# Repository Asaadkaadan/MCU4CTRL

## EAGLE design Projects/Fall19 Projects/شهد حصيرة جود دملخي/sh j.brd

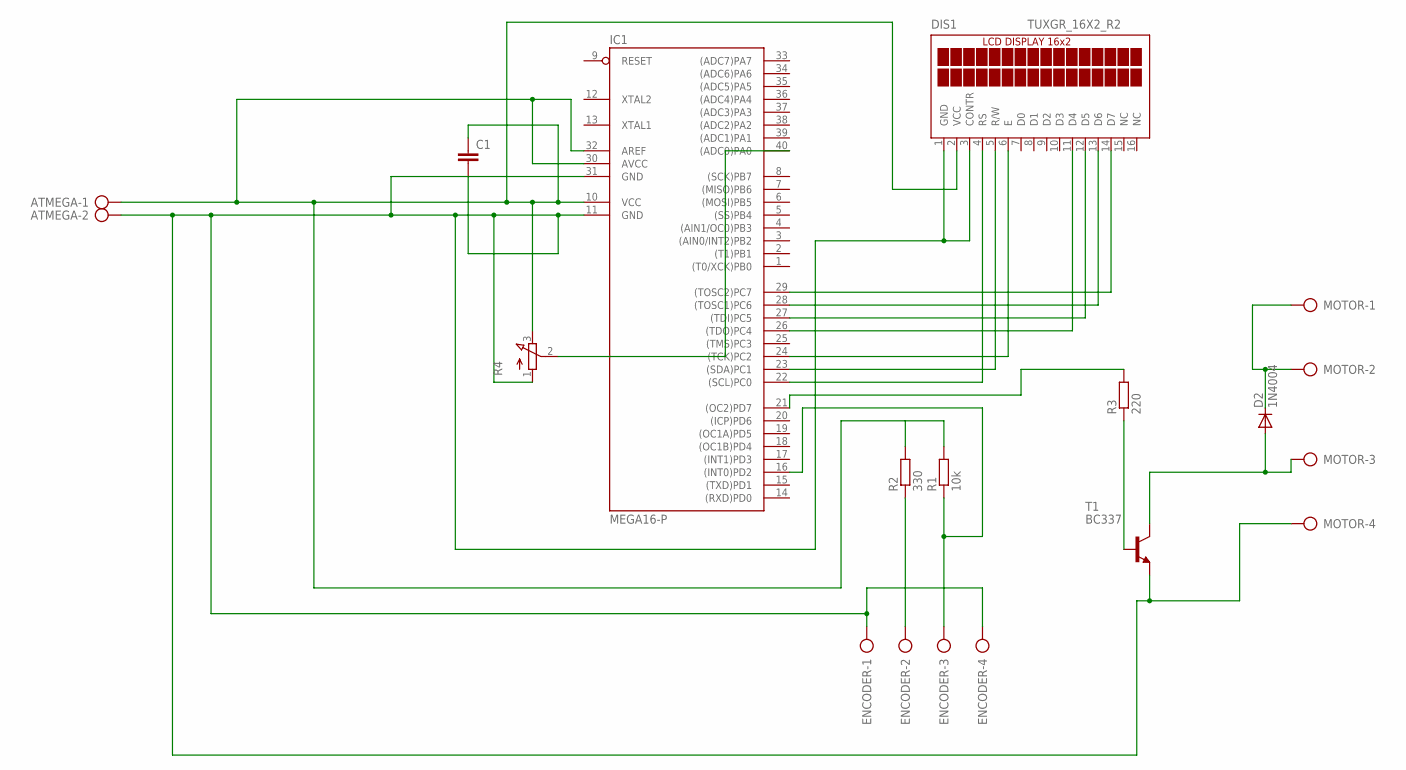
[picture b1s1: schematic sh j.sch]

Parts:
ATMEGA: AK500/2-H
C1: C-EU025-050X050; C025-050X050
D2: 1N4004; DO41-10
DIS1: TUXGR_16X2_R2
ENCODER: AK500/4-H
IC1: MEGA16-P; DIL40
MOTOR: AK500/4-H
R1: 10k; 0207/10
R2: 330; 0207/10
R3: 220; 0207/10
R4: 3RP/1610N
T1: BC337; TO92

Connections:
unnamed: DIS1.14 (D7), IC1.29 ((TOSC2)PC7)
unnamed: DIS1.13 (D6), IC1.28 ((TOSC1)PC6)
unnamed: DIS1.12 (D5), IC1.27 ((TDI)PC5)
unnamed: DIS1.11 (D4), IC1.26 ((TDO)PC4)
unnamed: DIS1.6 (E), IC1.24 ((TCK)PC2)
unnamed: DIS1.5 (R/W), IC1.23 ((SDA)PC1)
unnamed: DIS1.4 (RS), IC1.22 ((SCL)PC0)
unnamed: ATMEGA.2, C1.2, DIS1.1 (GND), DIS1.3 (CONTR), ENCODER.1, ENCODER.4, IC1.11 (GND), IC1.31 (GND), MOTOR.4, R4.1 (A), T1.1 (E)
unnamed: R3.1, T1.2 (B)
unnamed: IC1.21 ((OC2)PD7), R3.2
unnamed: ENCODER.3, IC1.16 ((INT0)PD2), R1.1
unnamed: D2.C, MOTOR.1, MOTOR.2
unnamed: D2.A, MOTOR.3, T1.3 (C)
unnamed: IC1.40 ((ADC0)PA0), R4.2 (S)
unnamed: ENCODER.2, R2.1
unnamed: ATMEGA.1, C1.1, DIS1.2 (VCC), IC1.10 (VCC), IC1.30 (AVCC), IC1.32 (AREF), R1.2, R2.2, R4.3 (E)

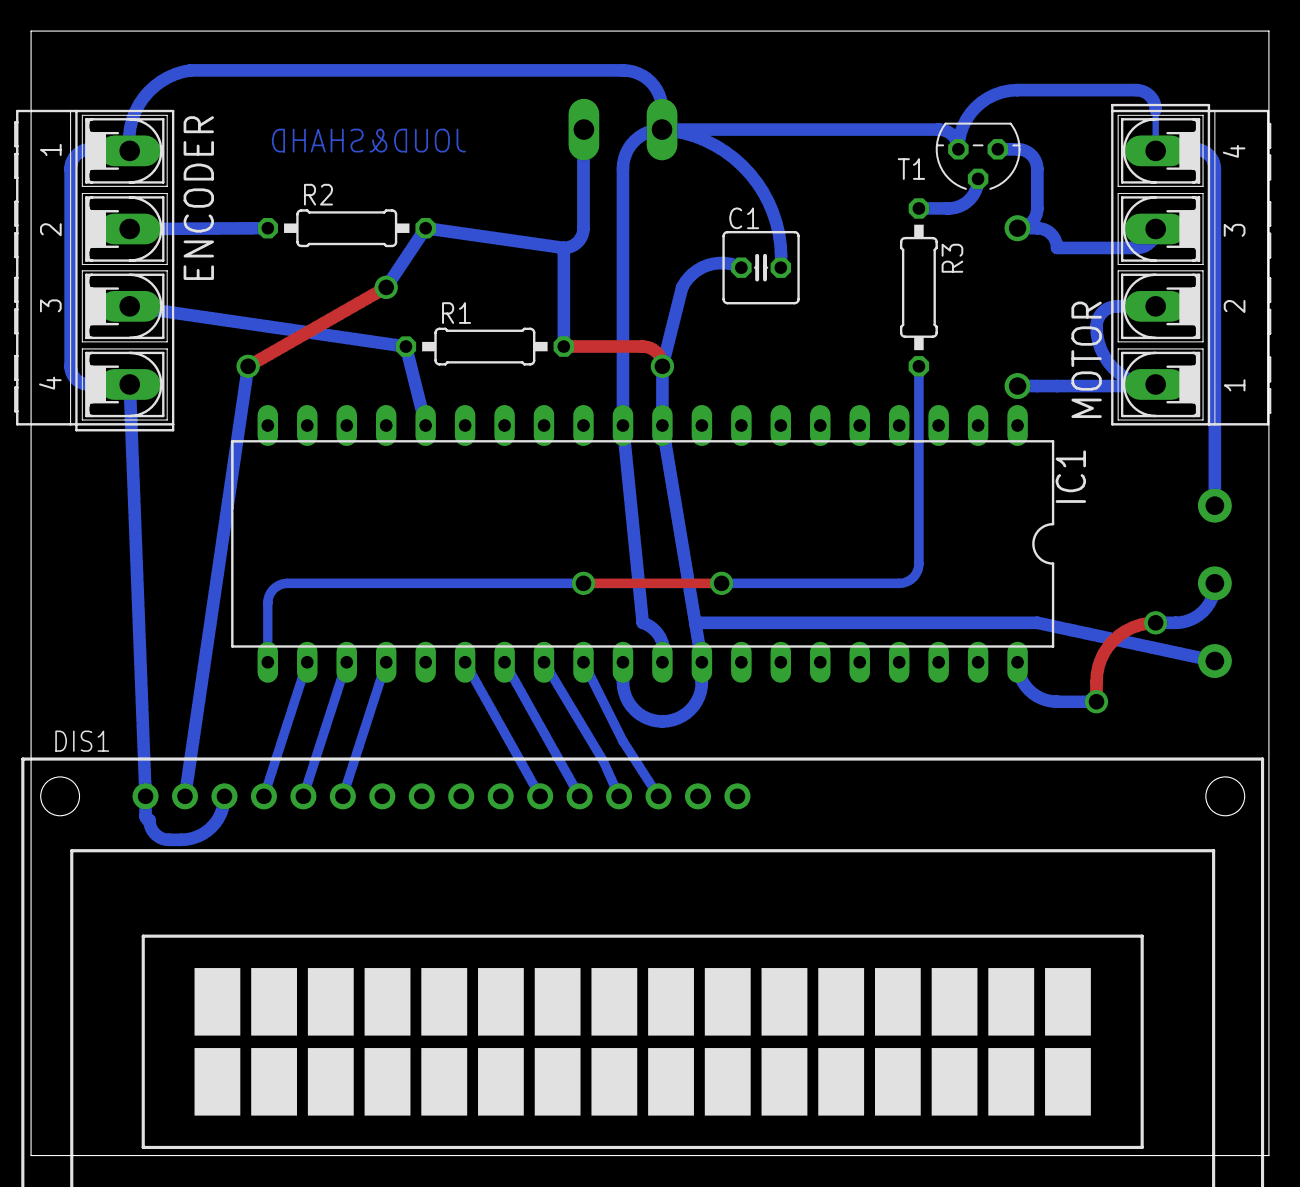
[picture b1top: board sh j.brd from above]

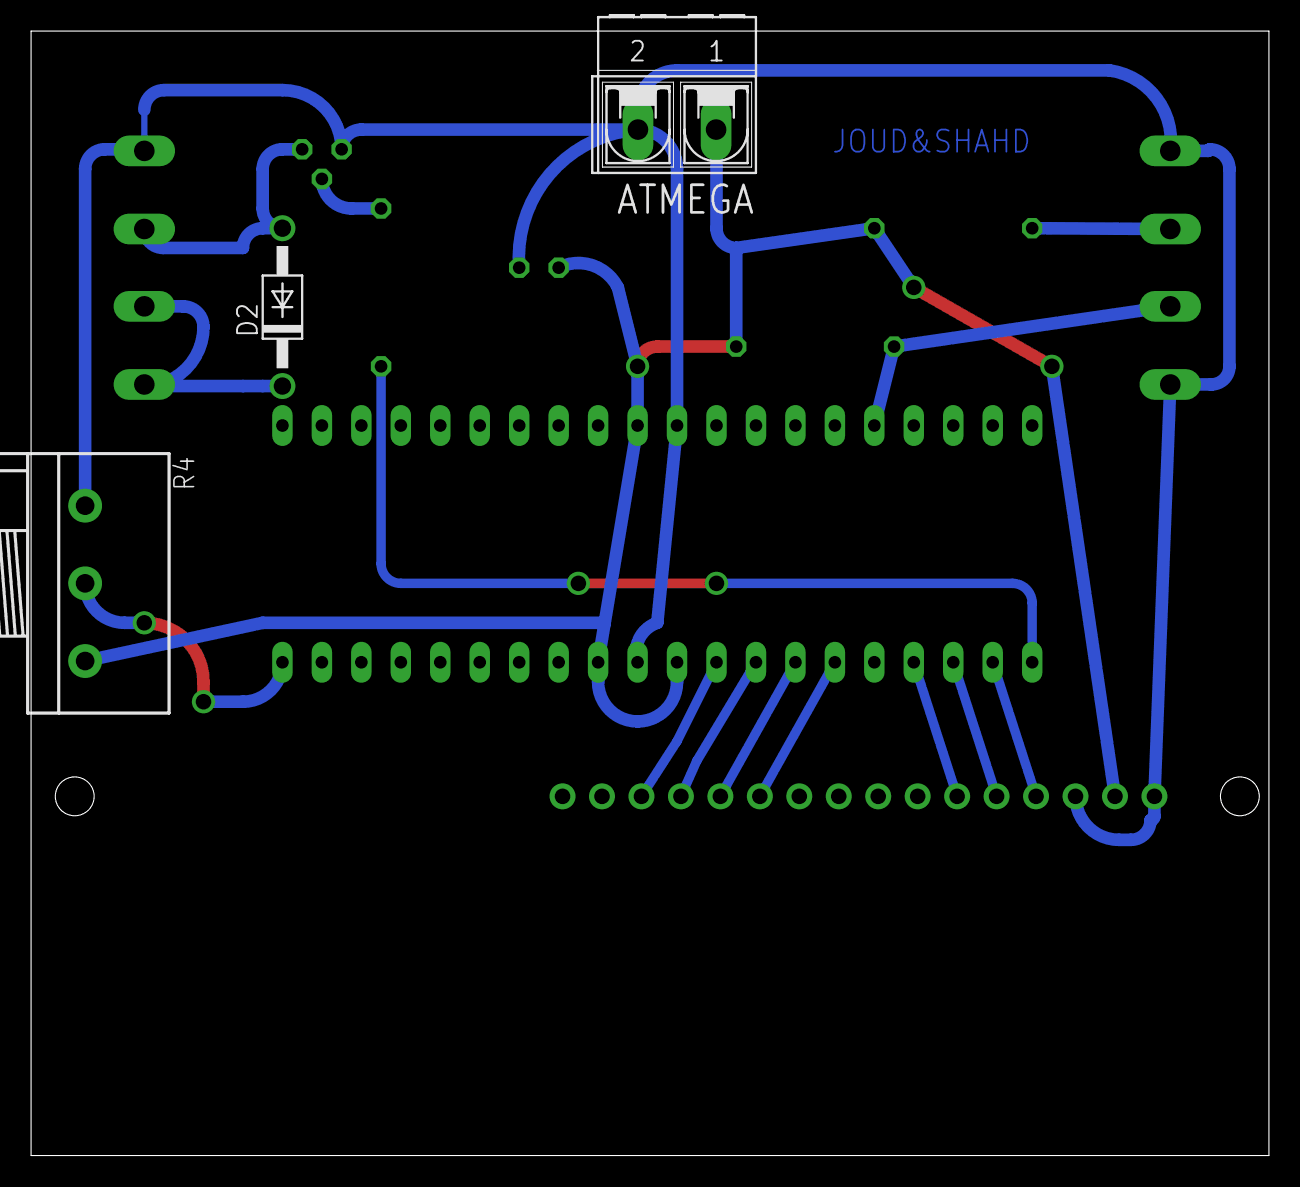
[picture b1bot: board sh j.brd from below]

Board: 2 copper layers, 79.7 x 72.4 mm, 12 parts (3 on the bottom side), 16 nets.

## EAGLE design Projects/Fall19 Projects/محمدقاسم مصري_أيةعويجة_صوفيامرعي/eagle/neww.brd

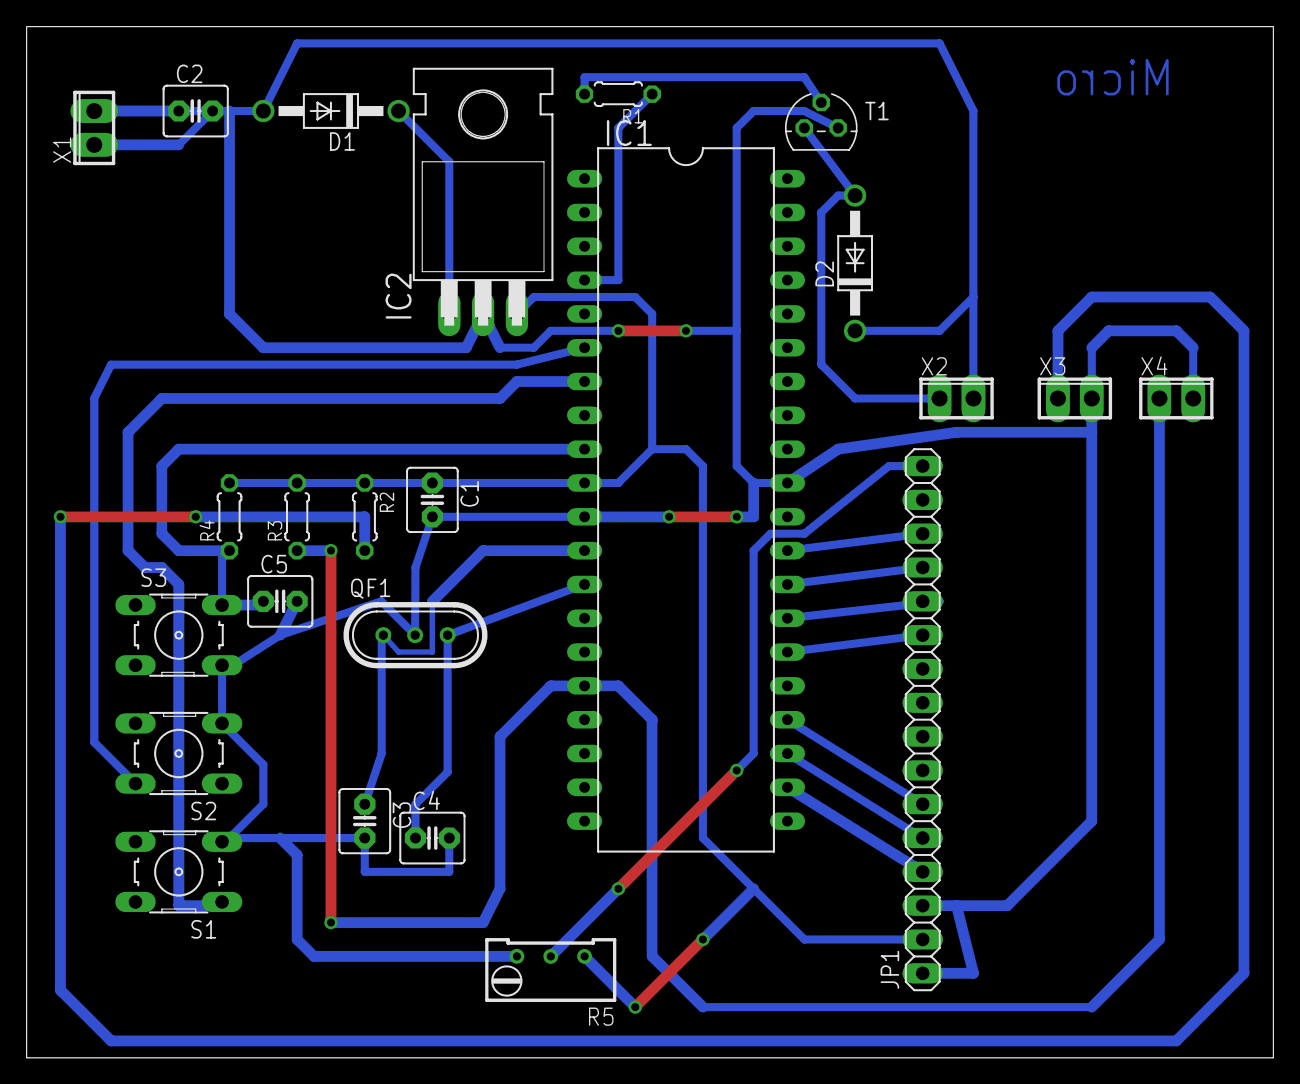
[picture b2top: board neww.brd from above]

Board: 2 copper layers, 93.7 x 77.5 mm, 24 parts (0 on the bottom side), 22 nets.

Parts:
C1, C2, C3, C4, C5: 100n; C2.5-4
D1, D2: 1N4004; DO41-10
IC1: MEGA16-P; DIL40
IC2: 7805T; TO220H
JP1: 1X16
QF1: IXFA; HC49U
R1: 1k; 0204/5
R2: 330; 0204/5
R3, R4: 10k; 0204/5
R5: RTRIM64W
S1, S2, S3: 5v; B3F-10XX
T1: BC337; TO92
X1, X2: 9; 2POL254
X3, X4: 5; 2POL254

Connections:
GND: C1.2, C2.2, C3.2, C4.2, C5.2, IC1.11, IC1.31, IC2.2, JP1.1, JP1.3, QF1.2, R5.3, S1.3, S2.3, S3.4, T1.1, X1.1, X3.2, X4.2
unnamed: R2.2, X3.1
unnamed: D1.C, IC2.1
unnamed: IC1.6, S2.2
unnamed: C1.1, IC1.10, IC2.3, JP1.2, R2.1, R3.2, R4.2, R5.1
unnamed: IC1.22, JP1.4
unnamed: IC1.23, JP1.5
unnamed: IC1.4, R1.1
unnamed: IC1.16, R3.1, X4.1
unnamed: R1.2, T1.2
unnamed: IC1.24, JP1.6
unnamed: C5.1, IC1.9, R4.1, S3.2
unnamed: D2.A, T1.3, X2.1
unnamed: IC1.26, JP1.11
unnamed: IC1.27, JP1.12
unnamed: IC1.28, JP1.13
unnamed: IC1.29, JP1.14
unnamed: IC1.7, S1.1
unnamed: C3.1, IC1.12, QF1.1
unnamed: C4.1, IC1.13, QF1.3
unnamed: C2.1, D1.A, D2.C, X1.2, X2.2
unnamed: JP1.16, R5.2
